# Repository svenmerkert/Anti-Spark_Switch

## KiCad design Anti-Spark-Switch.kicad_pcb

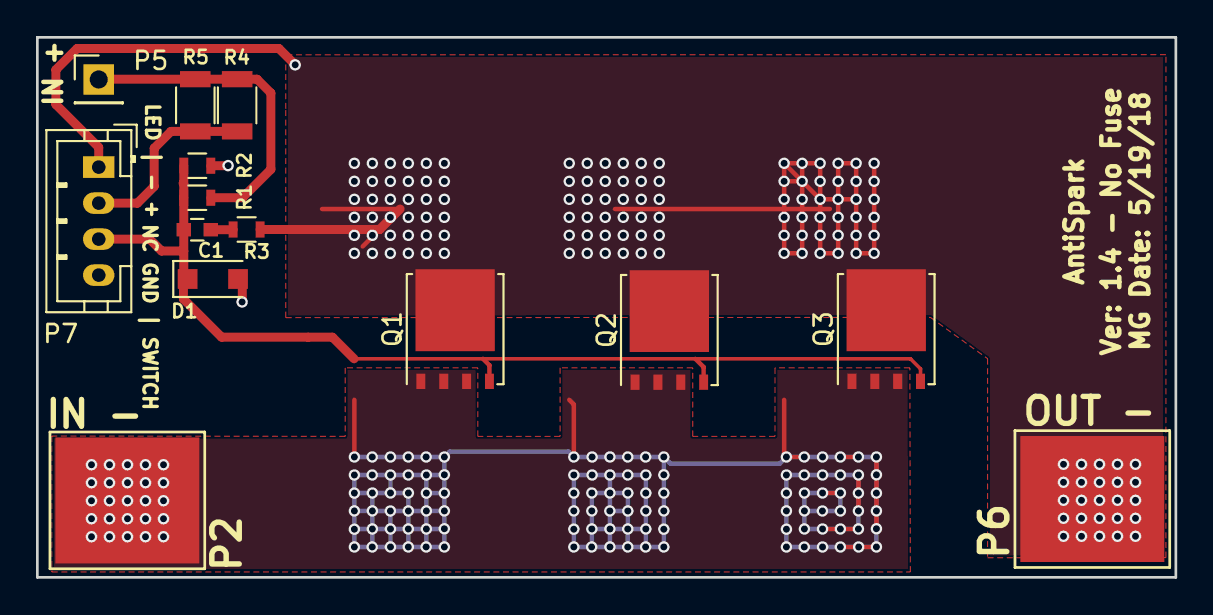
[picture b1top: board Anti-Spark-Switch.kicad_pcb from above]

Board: 2 copper layers, 63.2 x 30.0 mm, 14 parts (0 on the bottom side), 6 nets.

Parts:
C1: 1uF; C_0603
D1: ZENER; D_SOD-123F
P2, P6: Pad_Conn; 1PAD_8x7mm
P5: Pad_Conn; PinHeader_1x01_P2.54mm_Vertical
P7: CONN_01X04; JST_PH_B4B-PH-K_1x04_P2.00mm_Vertical
Q1, Q2, Q3: BSC026N08NS5; TDSON-8-1
R1, R2: 1M; R_0603
R3: 1K; R_0603
R4, R5: 16.5K; R_1206

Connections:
/SW_NC: C1.2, D1.1 (K), P7.3, Q1.4 (G), Q2.4 (G), Q3.4 (G), R1.2, R2.1
GND: D1.2 (A), P2.1, P7.4, Q1.1 (S), Q1.2 (S), Q1.3 (S), Q2.1 (S), Q2.2 (S), Q2.3 (S), Q3.1 (S), Q3.2 (S), Q3.3 (S), R2.2
unnamed: C1.1, R3.2
unnamed: P6.1, P7.1, Q1.5 (D), Q2.5 (D), Q3.5 (D), R3.1
unnamed: P7.2, R4.2, R5.2
VCC: P5.1, R1.1, R4.1, R5.1

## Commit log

2023-07-10 change mosfet to BSC026N08NS5
